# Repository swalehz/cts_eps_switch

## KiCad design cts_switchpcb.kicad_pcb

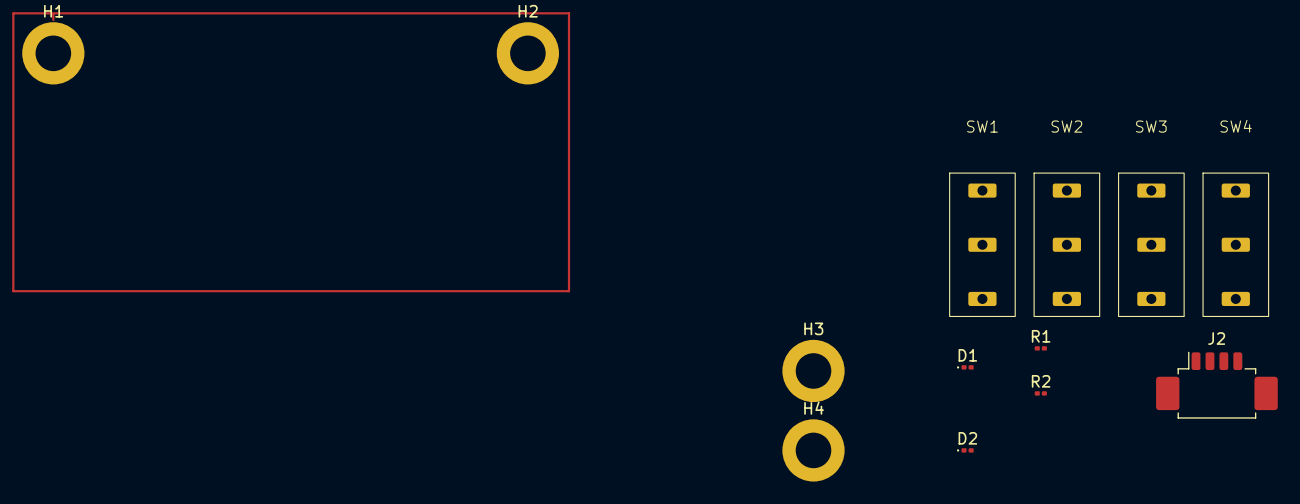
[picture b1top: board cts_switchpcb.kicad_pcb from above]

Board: 2 copper layers, 13 parts (0 on the bottom side), 5 nets, no tracks yet.

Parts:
D1, D2: LED; LED_0201_0603Metric
H1, H2, H3, H4: MountingHole_Pad; MountingHole_3.2mm_M3_DIN965_Pad
J2: Conn_01x06; Molex_PicoBlade_53261-0471_1x04-1MP_P1.25mm_Horizontal
R1, R2: R; R_0201_0603Metric
SW1, SW2, SW3, SW4: SW_SPDT; D2F_L3_D3_THT

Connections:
/!SEP1: J2.1, R1.1, SW1.3, SW2.3
/!SEP2: J2.3, R2.1, SW3.3, SW4.3
GND: D1.1 (K), D2.1 (K), H1.1, H2.1, H3.1, H4.1, J2.2, J2.4, J2.5, J2.6, SW1.1, SW2.1, SW3.1, SW4.1
unnamed: D1.2 (A), R1.2
unnamed: D2.2 (A), R2.2

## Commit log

2025-09-06 Skibidi toilet
